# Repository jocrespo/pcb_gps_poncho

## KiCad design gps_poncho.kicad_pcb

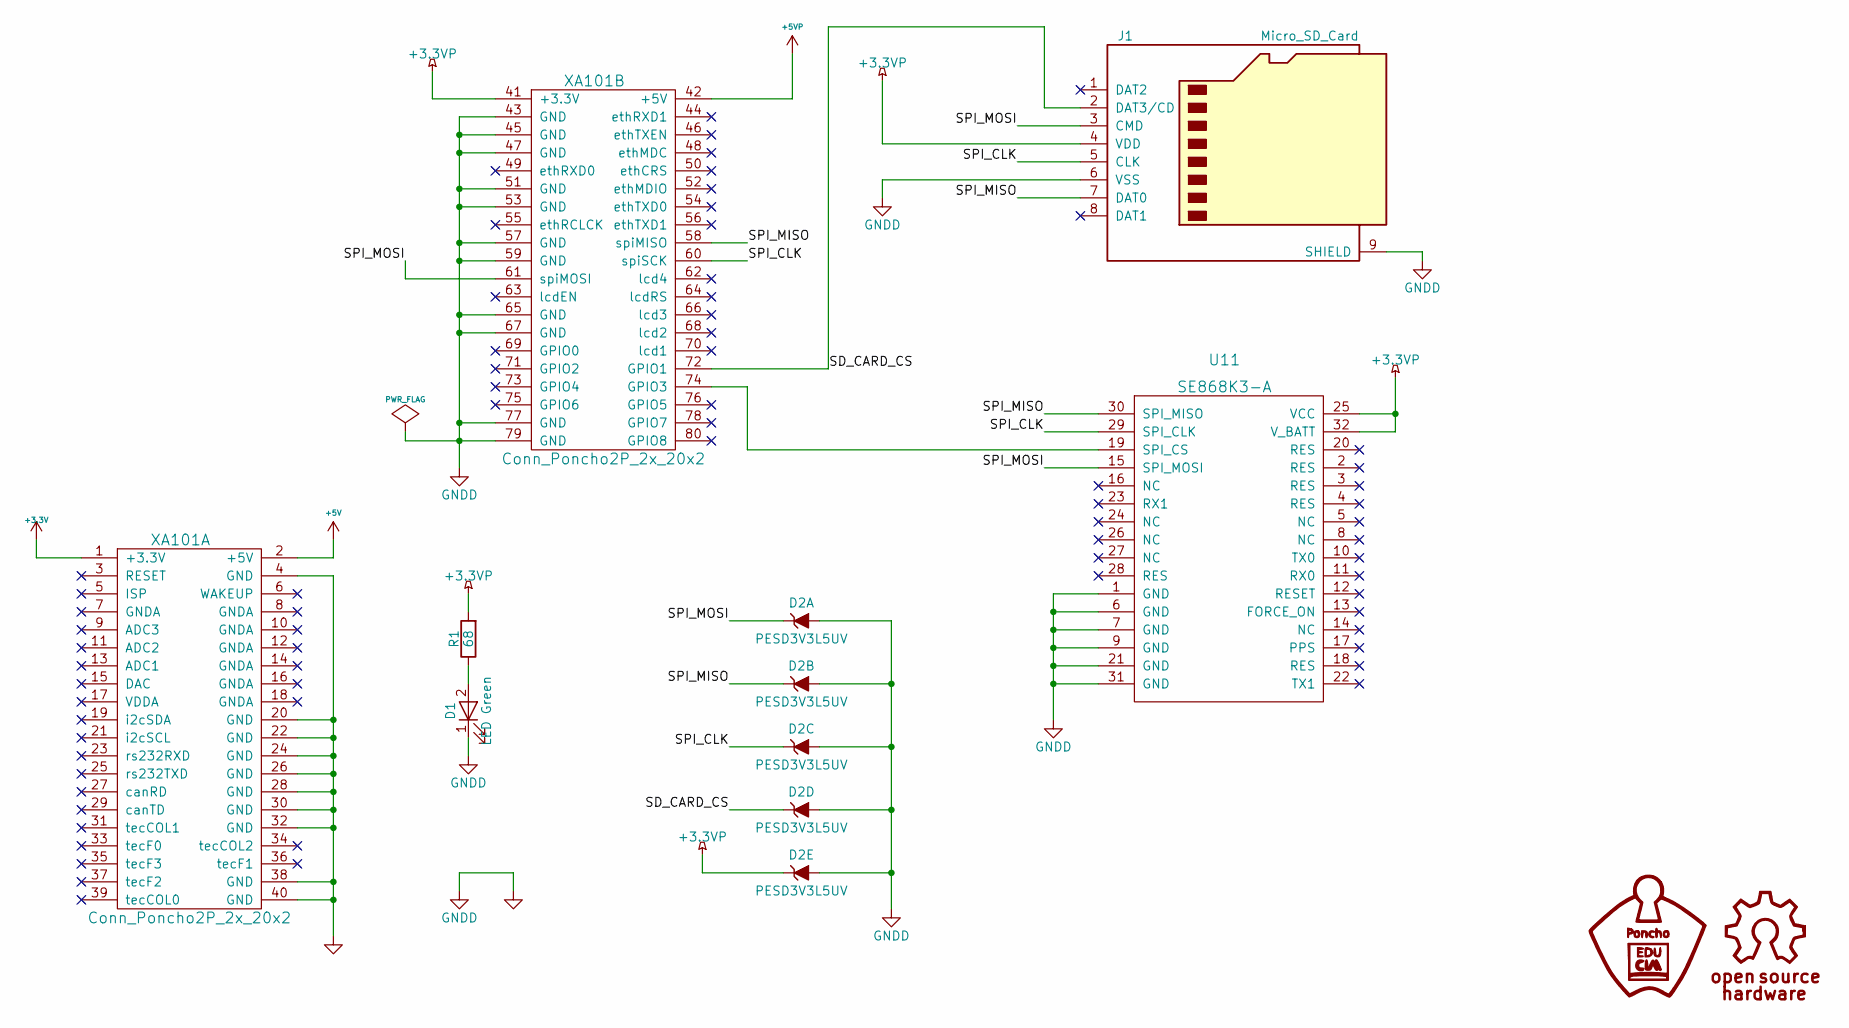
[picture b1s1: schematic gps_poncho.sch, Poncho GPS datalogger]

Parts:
D1: LED Green; LED_0805; Digikey# 1080-1411-1-ND
D2: PESD3V3L5UV; SOT-666; Digikey# 1727-5314-1-ND
J1: Micro_SD_Card; microSD_Card_Receptacle_Wuerth_693072010801; DigiKey# 732-3820-1-ND
R1: 68; R_0805; Digikey# RMCF0805JT68R0TR-ND
U11: SE868K3-A; se868A
XA101: Conn_Poncho2P_2x_20x2; Conn_Poncho_SinBorde; Digikey# 952-1387-ND

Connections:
+3.3VP: D2.6 (K5), J1.4 (VDD), R1.2, U11.25 (VCC), U11.32 (V_BATT), XA101.41 (+3.3V)
+3V3: XA101.1 (+3.3V)
+5V: XA101.2 (+5V)
+5VP: XA101.42 (+5V)
/SD_CARD_CS: D2.5 (K4), J1.2 (DAT3/CD), XA101.72 (GPIO1)
/SPI_CLK: D2.4 (K3), J1.5 (CLK), U11.29 (SPI_CLK), XA101.60 (spiSCK)
/SPI_MISO: D2.3 (K2), J1.7 (DAT0), U11.30 (SPI_MISO), XA101.58 (spiMISO)
/SPI_MOSI: D2.1 (K1), J1.3 (CMD), U11.15 (SPI_MOSI), XA101.61 (spiMOSI)
GND: D1.1 (K), D2.2 (A), J1.6 (VSS), J1.9 (SHIELD), U11.1 (GND), U11.6 (GND), U11.7 (GND), U11.9 (GND), U11.21 (GND), U11.31 (GND), XA101.4 (GND), XA101.20 (GND), XA101.22 (GND), XA101.24 (GND), XA101.26 (GND), XA101.28 (GND), XA101.30 (GND), XA101.32 (GND), XA101.38 (GND), XA101.40 (GND), XA101.43 (GND), XA101.45 (GND), XA101.47 (GND), XA101.51 (GND), XA101.53 (GND), XA101.57 (GND), XA101.59 (GND), XA101.65 (GND), XA101.67 (GND), XA101.77 (GND), XA101.79 (GND)
unnamed: D1.2 (A), R1.1
unnamed: U11.19 (SPI_CS), XA101.74 (GPIO3)

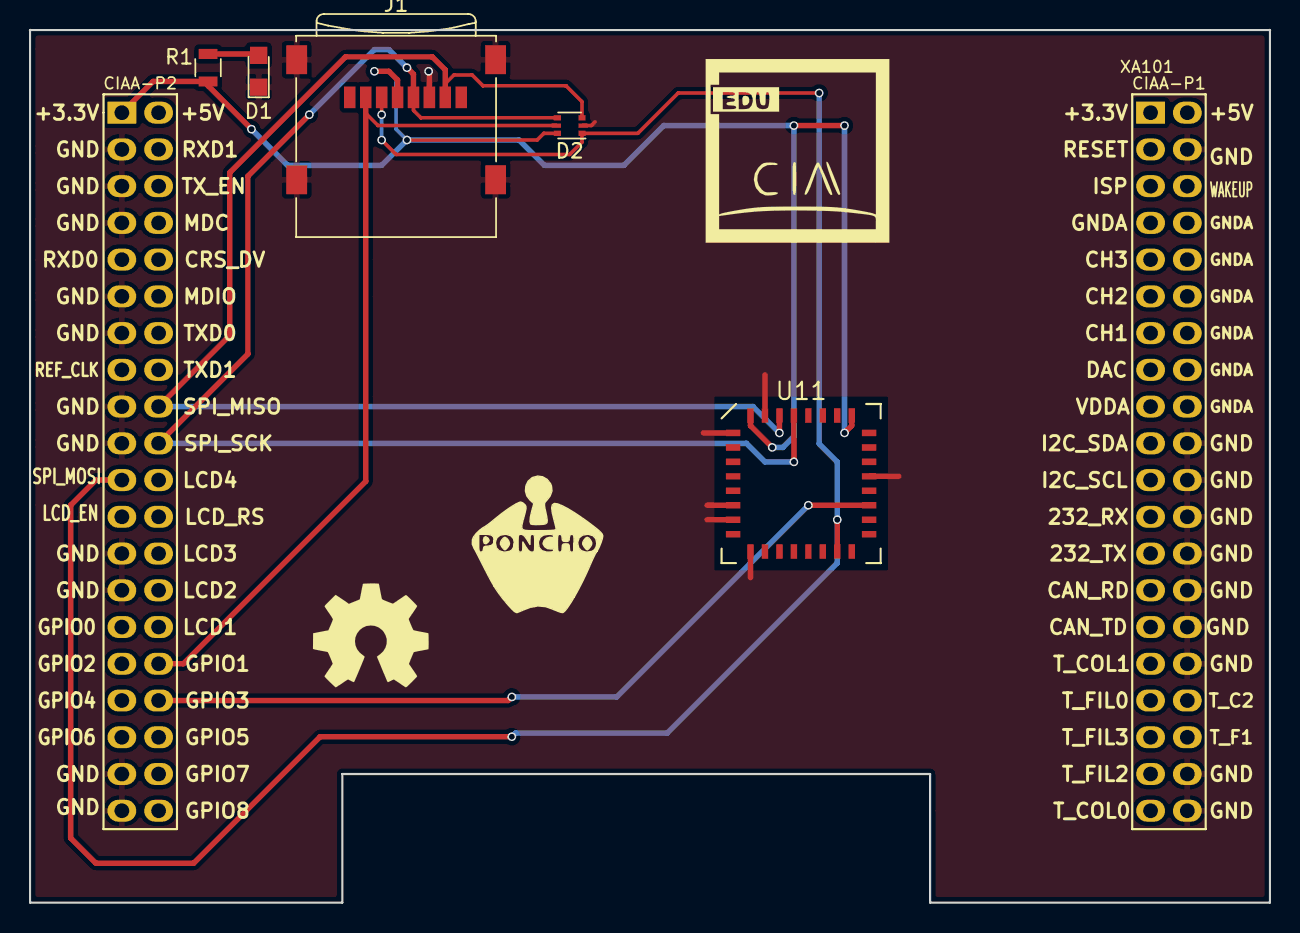
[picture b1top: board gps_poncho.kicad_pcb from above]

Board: 2 copper layers, 85.7 x 60.3 mm, 7 parts (0 on the bottom side), 8 nets.

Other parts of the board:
G101: Logo_OSHWA

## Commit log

2017-09-18 Primer commit
2017-09-25 Carpeta de documentacion added
2017-09-25 Cambio de nombre de proyecto
2017-09-25 Creacion de libreria del SL876Q5
2017-09-28 Cambio de chip gps y modelo de poncho
2017-10-09 Cambio de modelo de poncho inicial: Uso modelo Basico
2017-10-22 Se completa esquematico
2017-10-23 Simplifico conexiones de los conectores laterales
2017-10-23 Added datasheets: resistor and led
2017-10-24 Se retiran las librerias globales exportando a la carpeta del proyecto lib/
2017-10-24 Se añaden documentos de Licencia y Leeme
2017-10-24 Se toma en cuenta correcciones.Se referencian datasheet de los componentes
2017-10-25 Added pinout edu-ciaa para referencia
2017-10-31 Se añaden footprints y se toma en cuenta revisión de Victor Stalla. Se cambia slot de sd card
2017-11-02 Primera version de PCB
2017-11-10 Revision del PCB
